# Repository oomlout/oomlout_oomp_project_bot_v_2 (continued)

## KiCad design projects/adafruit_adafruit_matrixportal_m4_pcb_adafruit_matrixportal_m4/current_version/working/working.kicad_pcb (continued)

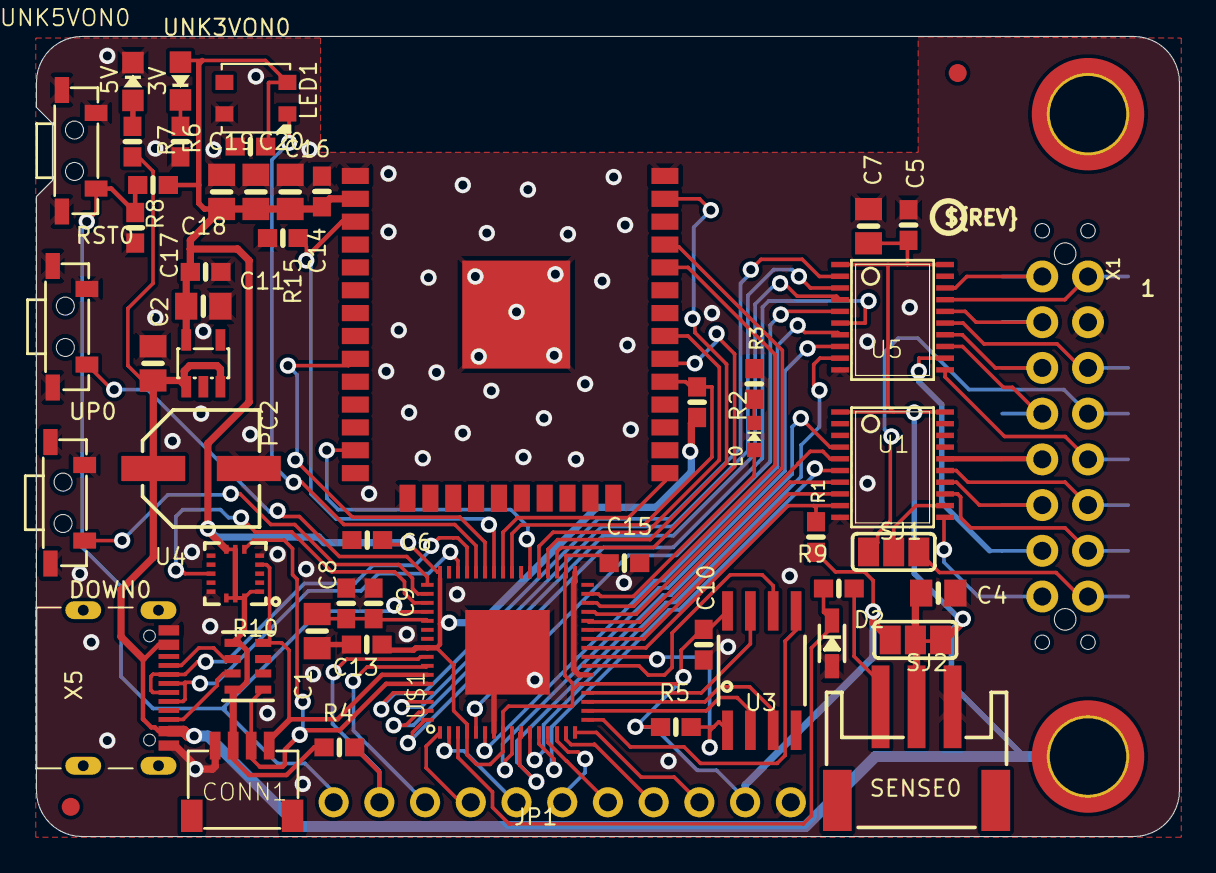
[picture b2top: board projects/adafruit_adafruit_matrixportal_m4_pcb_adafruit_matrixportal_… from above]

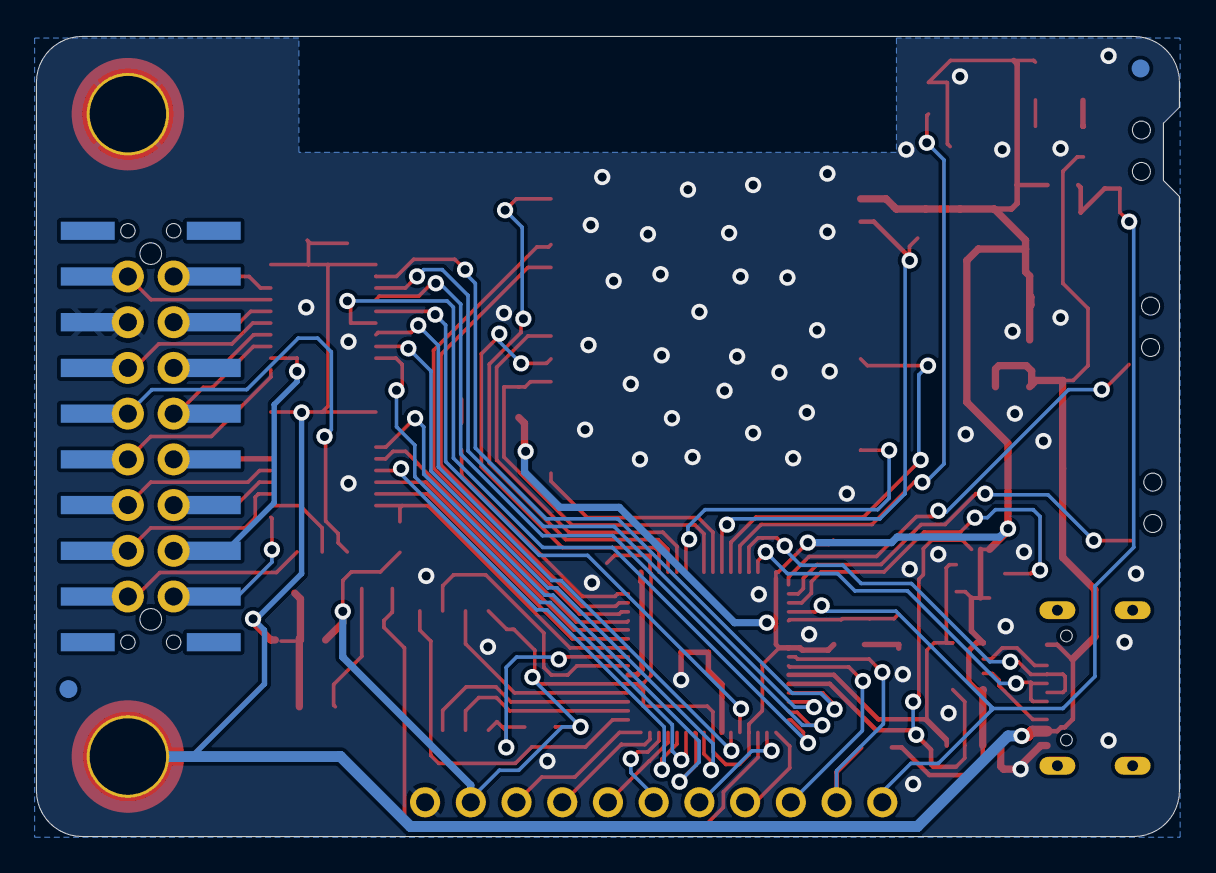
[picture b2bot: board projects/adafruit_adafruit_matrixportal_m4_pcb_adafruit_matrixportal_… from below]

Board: 2 copper layers, 63.5 x 44.5 mm, 62 parts (3 on the bottom side), 76 nets.

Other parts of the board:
U$41: MATRIXPORTAL_BOT
U$44: PCBFEAT-REV-040
U$45: MATRIXPORTAL_TOP

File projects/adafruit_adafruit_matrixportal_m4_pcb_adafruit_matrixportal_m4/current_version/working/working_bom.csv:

"Id";"Designator";"Footprint";"Quantity";"Designation";"Supplier and ref";
1;"R4,R9";"0603-NO";2;"1K";;;
2;"SENSE0";"JSTPH3";1;"JST PH 3";;;
3;"C3,C7,C2,C4,C19,C1,C18,C20";"0805-NO";8;"10uF";;;
4;"L0";"CHIPLED_0603_NOOUTLINE";1;"RED";;;
5;"U2";"SOT23-DBV";1;"AP2112K-3.3";;;
6;"D2";"SOD-323";1;"3.6V";;;
7;"C16,C6,C15,C11,C8,C10,C14";"0603-NO";7;".1u";;;
8;"C5,C17,C13";"0603-NO";3;"0.1uF";;;
9;"U$44";"PCBFEAT-REV-040";1;"";;;
10;"RST0,UP0,DOWN0";"SPST_TACTILE_RA";3;"TL3330AF260QG";;;
11;"TP2,TP1";"SMT_NUT_3MM";2;"SEWTAP_SMTNUTM3";;;
12;"LED1";"LED3535";1;"WS2812B3535";;;
13;"R15,R5,R1,R2,R6,R7";"0603-NO";6;"10K";;;
14;"U3";"SOIC8_208MIL";1;"GD25Q16";;;
15;"CONN1";"JST_SH4";1;"STEMMA_I2C_QT";;;
16;"X6";"WROOM32";1;"ESP32_WROOM32";;;
17;"R8,R3";"0603-NO";2;"5.1K";;;
18;"UNK3VON0,UNK5VON0";"CHIPLED_0805_NOOUTLINE";2;"GREEN";;;
19;"SJ2,SJ1";"SOLDERJUMPER_2WAY_OPEN_NOPASTE";2;"";;;
20;"FID2,FID1,FID3,FID4";"FIDUCIAL_1MM";4;"FIDUCIAL_1MM";;;
21;"JP1";"1X11_ROUND";1;"";;;
22;"U$45";"MATRIXPORTAL_TOP";1;"";;;
23;"U$1";"PQFN64-1";1;"ATSAMD51J19";;;
24;"R10";"RESPACK_4X0603";1;"5.1K";;;
25;"PC2";"PANASONIC_D";1;"47uF+/6.3V+";;;
26;"C9";"0603-NO";1;"1uF";;;
27;"U5,U1";"TSSOP20";2;"74AHCT245";;;
28;"X5";"USB_C_CUSB31-CFM2AX-01-X";1;"USB TYPE C";;;
29;"U4";"LGA16_3X3MM";1;"LIS3DHTR";;;
30;"X1";"2X08_SMTTHM_RGBMATRIX";1;"RGBMATRIX_THMSMT";;;
31;"U$41";"MATRIXPORTAL_BOT";1;"";;;

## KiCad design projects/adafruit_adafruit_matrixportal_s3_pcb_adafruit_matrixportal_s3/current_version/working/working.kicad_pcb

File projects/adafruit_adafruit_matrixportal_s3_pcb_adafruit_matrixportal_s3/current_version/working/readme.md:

# adafruit_matrixportal_s3_pcb
 
## summary 
* id: adafruit_adafruit_matrixportal_s3_pcb_adafruit_matrixportal_s3
* user: adafruit
* name: adafruit_matrixportal_s3_pcb
* board: adafruit_matrixportal_s3
* repo: https://github.com/adafruit/Adafruit-MatrixPortal-S3-PCB

* src_file_repo_sch: 
* src_file_repo_sch_link: https://github.com/adafruit/Adafruit-MatrixPortal-S3-PCB/tree/main/
* full details link: https://github.com/oomlout/oomlout_oomp_project_bot_v_2/tree/main/projects/adafruit_adafruit_matrixportal_s3_pcb_adafruit_matrixportal_s3/current_version/working  

## schematic  
  
[schematic (pdf)](working_schematic.pdf) 

## pcb  

[board (pdf)](working.pdf)  

## working_bom
| Id | Designator | Footprint | Quantity | Designation | Supplier and ref |  | None | 
| --- | --- | --- | --- | --- | --- | --- | --- | 
| 1 | SW1 | BTN_RKB2_4.6X2.8 | 1 | KMR2 |  |  | [''] | 
| 2 | C10,C14,C5,C15,C11 | 0603-NO | 5 | 0.1uF |  |  | [''] | 
| 3 | D2 | SOD-323 | 1 | 3.6V |  |  | [''] | 
| 4 | SJ1,SJ2 | SOLDERJUMPER_2WAY_OPEN_NOPASTE | 2 |  |  |  | [''] | 
| 5 | C23,C2,C18,C22,C7,C20,C19,C4,C3 | 0805-NO | 9 | 10uF |  |  | [''] | 
| 6 | U$25 | S3_MATRIXPORTAL_TOP | 1 |  |  |  | [''] | 
| 7 | UNK3VON0,UNK5VON0 | CHIPLED_0603_NOOUTLINE | 2 | GREEN |  |  | [''] | 
| 8 | CONN1 | JST_SH4 | 1 | STEMMA_I2C_QT |  |  | [''] | 
| 9 | C21,C24,C17 | 0603-NO | 3 | 1uF |  |  | [''] | 
| 10 | R10 | RESPACK_4X0603 | 1 | 5.1K Pack |  |  | [''] | 
| 11 | R16,R3,R1,R2,R7,R6 | 0603-NO | 6 | 10K |  |  | [''] | 
| 12 | SENSE0 | JSTPH3 | 1 | JST PH 3 |  |  | [''] | 
| 13 | LED1 | LED3535_FULLPADS | 1 | WS2812B_3535FULL |  |  | [''] | 
| 14 | U3 | S3-WROOM32 | 1 | ESP32-S3-WROOM |  |  | [''] | 
| 15 | U$44 | PCBFEAT-REV-040 | 1 |  |  |  | [''] | 
| 16 | L0 | CHIPLED_0603_NOOUTLINE | 1 | RED |  |  | [''] | 
| 17 | FID2,FID1,FID3,FID4 | FIDUCIAL_1MM | 4 | FIDUCIAL_1MM |  |  | [''] | 
| 18 | JP1 | 1X11_ROUND | 1 |  |  |  | [''] | 
| 19 | U$14,U$22,U$24,U$19 | MOUNTINGHOLE_2.5_PLATED | 4 | MOUNTINGHOLE2.5 |  |  | [''] | 
| 20 | U1,U5 | TSSOP20 | 2 | 74AHCT245 |  |  | [''] | 
| 21 | UP0,DOWN0,RST0 | SPST_TACTILE_RA | 3 | TL3330AF260QG |  |  | [''] | 
| 22 | TP2,TP1 | SMT_NUT_3MM | 2 | SEWTAP_SMTNUTM3 |  |  | [''] | 
| 23 | R9 | 0603-NO | 1 | 1K |  |  | [''] | 
| 24 | U6 | ALS-PT19-315C | 1 | ALS-PT19 |  |  | [''] | 
| 25 | PC2 | PANASONIC_D | 1 | 100uF/6.3V |  |  | [''] | 
| 26 | U2 | SOT23-DBV | 1 | AP2112K-3.3 |  |  | [''] | 
| 27 | R17 | 0603-NO | 1 | 1Meg |  |  | [''] | 
| 28 | U4 | LGA16_3X3MM | 1 | LIS3DHTR |  |  | [''] | 
| 29 | JP2 | 2X08_SHROUDEDSMT | 1 | 2x8_SMT_IDC |  |  | [''] | 
| 30 | X5 | USB_C_CUSB31-CFM2AX-01-X | 1 | USB TYPE C |  |  | [''] | 
| 31 | U$26 | S3_MATRIXPORTAL_BOT | 1 |  |  |  | [''] | 
| 32 | JP3 | 2X10_SMT_FEMALE | 1 | 2x10_SMT_F |  |  | [''] | 

## bom_schematic
| Ref | Qnty | Value | Cmp name | Footprint | Description | Vendor | DNP | 
| --- | --- | --- | --- | --- | --- | --- | --- | 
| C2, C3, C4, C7, C18, C19, C20, C22, C23 | 9 | 10uF | CAP_CERAMIC0805-NOOUTLINE | working:0805-NO |  |  |  | 
| C5, C10, C11, C14, C15 | 5 | 0.1uF | CAP_CERAMIC0603_NO | working:0603-NO |  |  |  | 
| C17, C21, C24 | 3 | 1uF | CAP_CERAMIC0603_NO | working:0603-NO |  |  |  | 
| CONN1 | 1 | STEMMA_I2C_QT | STEMMA_I2C_QT | working:JST_SH4 |  |  |  | 
| D2 | 1 | 3.6V | DIODE-ZENERSOD323 | working:SOD-323 |  |  |  | 
| DOWN0 | 1 | TL3330AF260QG | SWITCH_SPST_MNT_TACT_RA | working:SPST_TACTILE_RA |  |  |  | 
| FID1, FID2, FID3, FID4 | 4 | FIDUCIAL_1MM | FIDUCIAL_1MM | working:FIDUCIAL_1MM |  |  |  | 
| JP1 | 1 | HEADER-1X11 | HEADER-1X11 | working:1X11_ROUND |  |  |  | 
| JP2 | 1 | 2x8_SMT_IDC | HEADER-2X8_SHROUDEDSMT | working:2X08_SHROUDEDSMT |  |  |  | 
| JP3 | 1 | 2x10_SMT_F | HEADER-2X10SMT_FEMALE | working:2X10_SMT_FEMALE |  |  |  | 
| L0 | 1 | RED | LED0603_NOOUTLINE | working:CHIPLED_0603_NOOUTLINE |  |  |  | 
| LED1 | 1 | WS2812B_3535FULL | WS2812B_3535FULL | working:LED3535_FULLPADS |  |  |  | 
| PC2 | 1 | 100uF/6.3V | CAP_ELECTROLYTICPANASONIC_D | working:PANASONIC_D |  |  |  | 
| R1, R2, R3, R6, R7, R16 | 6 | 10K | RESISTOR_0603_NOOUT | working:0603-NO |  |  |  | 
| R9 | 1 | 1K | RESISTOR_0603_NOOUT | working:0603-NO |  |  |  | 
| R10 | 1 | 5.1K Pack | RESISTOR_4PACK | working:RESPACK_4X0603 |  |  |  | 
| R17 | 1 | 1Meg | RESISTOR_0603_NOOUT | working:0603-NO |  |  |  | 
| RST0 | 1 | TL3330AF260QG | SWITCH_SPST_MNT_TACT_RA | working:SPST_TACTILE_RA |  |  |  | 
| SENSE0 | 1 | JST PH 3 | CON_JST_PH_3PIN | working:JSTPH3 |  |  |  | 
| SJ1, SJ2 | 2 | SOLDERJUMPER_2WAY | SOLDERJUMPER_2WAY | working:SOLDERJUMPER_2WAY_OPEN_NOPASTE |  |  |  | 
| SW1 | 1 | KMR2 | SWITCH_TACT_SMT_RKB2 | working:BTN_RKB2_4.6X2.8 |  |  |  | 
| TP1, TP2 | 2 | SEWTAP_SMTNUTM3 | SEWTAP_SMTNUTM3 | working:SMT_NUT_3MM |  |  |  | 
| U1, U5 | 2 | 74AHCT245 | 74LCX245_TSSOP20 | working:TSSOP20 |  |  |  | 
| U2 | 1 | LP2985-XXDBVR | LP2985-XXDBVR | working:SOT23-DBV |  |  |  | 
| U3 | 1 | ESP32-S3-WROOM | ESP32-S3-WROOM | working:S3-WROOM32 |  |  |  | 
| U4 | 1 | LIS3DHTR | ACCEL_LIS3DHTR | working:LGA16_3X3MM |  |  |  | 
| U6 | 1 | ALS-PT19 | PHOTOTRANSISTOR_PT19-315C | working:ALS-PT19-315C |  |  |  | 
| U$14, U$19, U$22, U$24 | 4 | MOUNTINGHOLE2.5 | MOUNTINGHOLE2.5 | working:MOUNTINGHOLE_2.5_PLATED |  |  |  | 
| UNK3VON0 | 1 | GREEN | LED0603_NOOUTLINE | working:CHIPLED_0603_NOOUTLINE |  |  |  | 
| UNK5VON0 | 1 | GREEN | LED0603_NOOUTLINE | working:CHIPLED_0603_NOOUTLINE |  |  |  | 
| UP0 | 1 | TL3330AF260QG | SWITCH_SPST_MNT_TACT_RA | working:SPST_TACTILE_RA |  |  |  | 
| X5 | 1 | USB TYPE C | USB_C | working:USB_C_CUSB31-CFM2AX-01-X |  |  |  | 

## mounting_holes
| x | y | package | value | ref | size | 
| --- | --- | --- | --- | --- | --- | 
| 0.0 | 0.0 | MOUNTINGHOLE_2.5_PLATED | MOUNTINGHOLE2.5 | U$14 | m3 | 
| 0.0 | 19.69 | MOUNTINGHOLE_2.5_PLATED | MOUNTINGHOLE2.5 | U$19 | m3 | 
| 40.64 | 19.69 | MOUNTINGHOLE_2.5_PLATED | MOUNTINGHOLE2.5 | U$22 | m3 | 
| 40.64 | 0.0 | MOUNTINGHOLE_2.5_PLATED | MOUNTINGHOLE2.5 | U$24 | m3 |

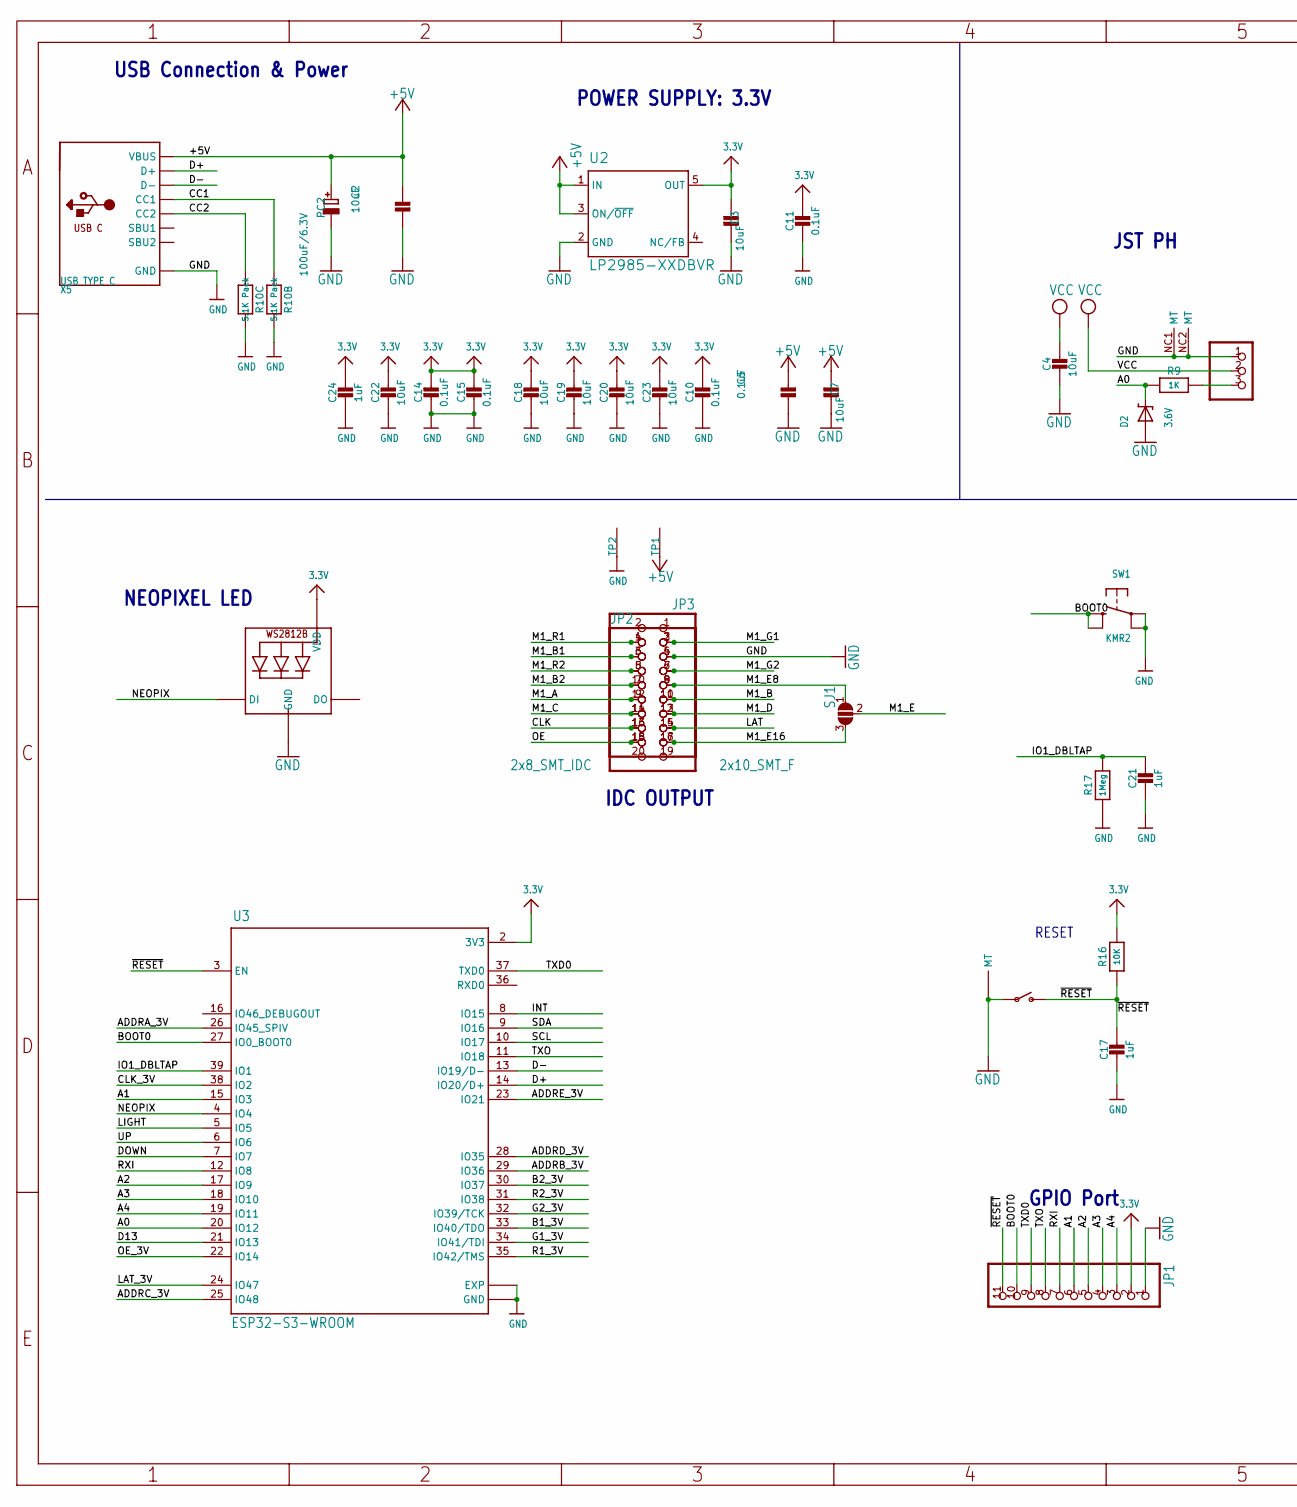
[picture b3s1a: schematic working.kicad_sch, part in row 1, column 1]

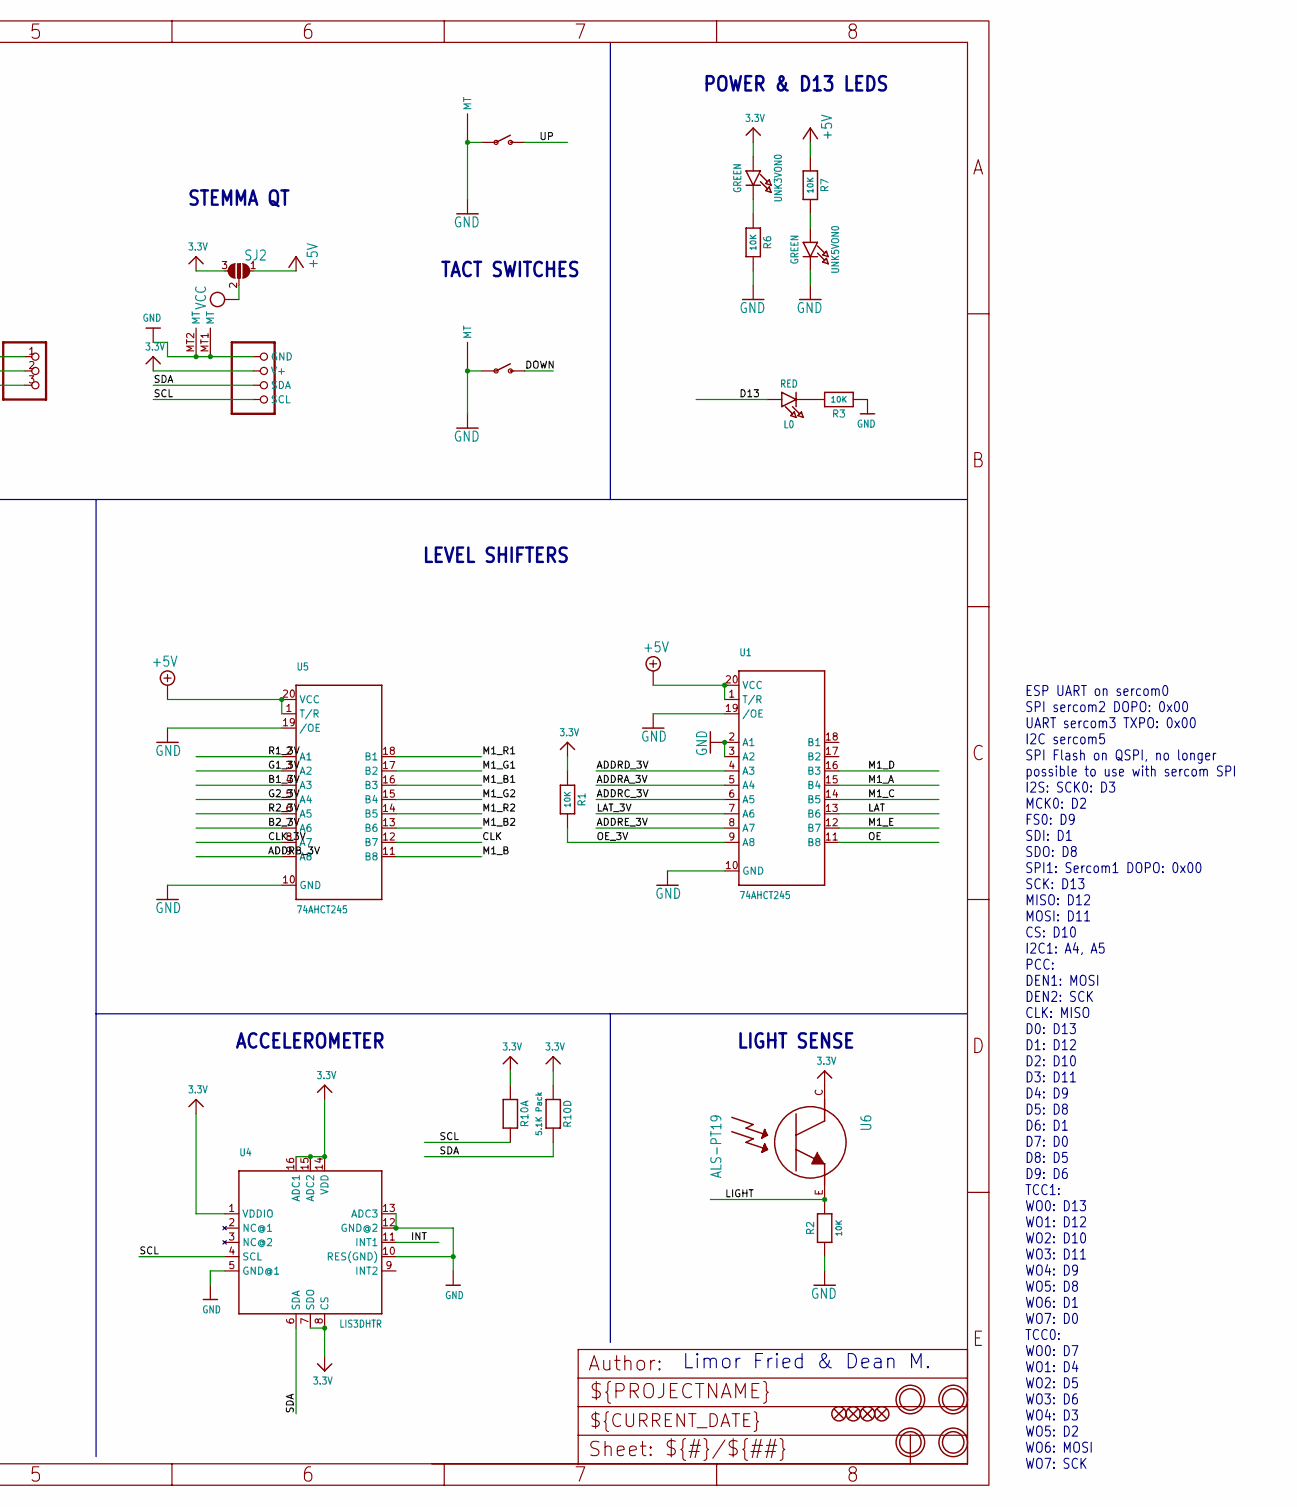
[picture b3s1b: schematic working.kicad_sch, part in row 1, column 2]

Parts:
C2, C3, C4, C7, C18, C19, C20, C22, C23: 10uF; 0805-NO
C5, C10, C11, C14, C15: 0.1uF; 0603-NO
C17, C21, C24: 1uF; 0603-NO
CONN1: STEMMA_I2C_QT; JST_SH4
D2: 3.6V; SOD-323
DOWN0: TL3330AF260QG; SPST_TACTILE_RA
FID1, FID2, FID3, FID4: FIDUCIAL_1MM
JP1: HEADER-1X11; 1X11_ROUND
JP2: 2x8_SMT_IDC; 2X08_SHROUDEDSMT
JP3: 2x10_SMT_F; 2X10_SMT_FEMALE
L0: RED; CHIPLED_0603_NOOUTLINE
LED1: WS2812B_3535FULL; LED3535_FULLPADS
PC2: 100uF/6.3V; PANASONIC_D
R1, R2, R3, R6, R7, R16: 10K; 0603-NO
R9: 1K; 0603-NO
R10: 5.1K Pack; RESPACK_4X0603
R17: 1Meg; 0603-NO
RST0: TL3330AF260QG; SPST_TACTILE_RA
SENSE0: JST PH 3; JSTPH3
SJ1, SJ2: SOLDERJUMPER_2WAY; SOLDERJUMPER_2WAY_OPEN_NOPASTE
SW1: KMR2; BTN_RKB2_4.6X2.8
TP1, TP2: SEWTAP_SMTNUTM3; SMT_NUT_3MM
U1, U5: 74AHCT245; TSSOP20
U2: LP2985-XXDBVR; SOT23-DBV
U3: ESP32-S3-WROOM; S3-WROOM32
U4: LIS3DHTR; LGA16_3X3MM
U6: ALS-PT19; ALS-PT19-315C
U$14, U$19, U$22, U$24: MOUNTINGHOLE2.5; MOUNTINGHOLE_2.5_PLATED
UNK3VON0, UNK5VON0: GREEN; CHIPLED_0603_NOOUTLINE
UP0: TL3330AF260QG; SPST_TACTILE_RA
X5: USB TYPE C; USB_C_CUSB31-CFM2AX-01-X

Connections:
3.3V: C3.2, C10.2, C11.2, C14.2, C15.2, C18.1, C19.1, C20.1, C22.1, C23.1, C24.1, CONN1.2 (V+), JP1.2, LED1.2 (VDD), R1.1, R10.1, R10.4 (1), R16.2, SJ2.3, U2.5 (OUT), U3.2 (3V3), U4.1 (VDDIO), U4.7 (SDO), U4.8 (CS), U4.14 (VDD), U4.15 (ADC2), U4.16 (ADC1), U6.C, UNK3VON0.A
+5V: C2.2, C5.2, C7.2, PC2.+, R7.1, SJ2.1, TP1.P$1, U1.1 (T/R), U1.20 (VCC), U2.1 (IN), U2.3 (ON/~OFF), U5.1 (T/R), U5.20 (VCC), X5.A4B9 (VBUS), X5.B4A9 (VBUS)
A0: D2.C, R9.2, U3.20 (IO12)
A0_JST: R9.1, SENSE0.3
A1: JP1.6, U3.15 (IO3)
A2: JP1.5, U3.17 (IO9)
A3: JP1.4, U3.18 (IO10)
A4: JP1.3, U3.19 (IO11)
ADDRA_3V: U1.5 (A4), U3.26 (IO45_SPIV)
ADDRB_3V: U3.29 (IO36), U5.9 (A8)
ADDRC_3V: U1.6 (A5), U3.25 (IO48)
ADDRD_3V: U1.4 (A3), U3.28 (IO35)
ADDRE_3V: U1.8 (A7), U3.23 (IO21)
B1_3V: U3.33 (IO40/TDO), U5.4 (A3)
B2_3V: U3.30 (IO37), U5.7 (A6)
BOOT0: JP1.10, SW1.B (S), SW1.B' (S1), U3.27 (IO0_BOOT0)
CC1: R10.2 (1), X5.A5 (CC1)
CC2: R10.3 (1), X5.B5 (CC2)
CLK: JP2.13, JP3.16, U5.12 (B7)
CLK_3V: U3.38 (IO2), U5.8 (A7)
D13: L0.A, U3.21 (IO13)
D+: U3.14 (IO20/D+), X5.A6 (D+), X5.B6 (D+)
D-: U3.13 (IO19/D-), X5.A7 (D-), X5.B7 (D-)
DOWN: DOWN0.2 (S), U3.7 (IO7)
G1_3V: U3.34 (IO41/TDI), U5.3 (A2)
G2_3V: U3.32 (IO39/TCK), U5.5 (A4)
GND: C2.1, C3.1, C4.2, C5.1, C7.1, C10.1, C11.1, C14.1, C15.1, C17.2, C18.2, C19.2, C20.2, C21.2, C22.2, C23.2, C24.2, CONN1.1 (GND), CONN1.MT1 (MT), CONN1.MT2 (MT), D2.A, DOWN0.1, DOWN0.MT1 (MT), DOWN0.MT2 (MT), JP1.1, JP2.4, JP3.5, LED1.4 (GND), PC2.-, R2.2, R3.2, R6.2, R10.6 (2), R10.7 (2), R17.1, RST0.1, RST0.MT1 (MT), RST0.MT2 (MT), SENSE0.1, SENSE0.NC1 (MT), SENSE0.NC2 (MT), SW1.A, SW1.A' (P1), TP2.P$1, U1.2 (A1), U1.3 (A2), U1.10 (GND), U1.19 (/OE), U2.2 (GND), U3.1 (GND), U3.40 (GND), U3.P$2 (EXP), U3.P$3 (EXP), U3.P$4 (EXP), U3.P$5 (EXP), U3.P$6 (EXP), U3.P$7 (EXP), U3.P$8 (EXP), U3.P$9 (EXP), U3.P$10 (EXP), U4.5 (GND@1), U4.10 (RES(GND)), U4.12 (GND@2), U4.13 (ADC3), U5.10 (GND), U5.19 (/OE), UNK5VON0.C, UP0.1, UP0.MT1 (MT), UP0.MT2 (MT), X5.A1B12 (GND), X5.B1A12 (GND)
INT: U3.8 (IO15), U4.11 (INT1)
IO1_DBLTAP: C21.1, R17.2, U3.39 (IO1)
LAT: JP2.14, JP3.15, U1.13 (B6)
LAT_3V: U1.7 (A6), U3.24 (IO47)
LIGHT: R2.1, U3.5 (IO5), U6.E
M1_A: JP2.9, JP3.12, U1.15 (B4)
M1_B: JP2.10, JP3.11, U5.11 (B8)
M1_B1: JP2.3, JP3.6, U5.16 (B3)
M1_B2: JP2.7, JP3.10, U5.13 (B6)
M1_C: JP2.11, JP3.14, U1.14 (B5)
M1_D: JP2.12, JP3.13, U1.16 (B3)
M1_E: SJ1.2, U1.12 (B7)
M1_E8: JP2.8, JP3.9, SJ1.1
M1_E16: JP2.16, JP3.17, SJ1.3
M1_G1: JP2.2, JP3.3, U5.17 (B2)
M1_G2: JP2.6, JP3.7, U5.15 (B4)
M1_R1: JP2.1, JP3.4, U5.18 (B1)
M1_R2: JP2.5, JP3.8, U5.14 (B5)
unnamed: R7.2, UNK5VON0.A
unnamed: R6.1, UNK3VON0.C
unnamed: L0.C, R3.1
NEOPIX: LED1.1 (DI), U3.4 (IO4)
OE: JP2.15, JP3.18, U1.11 (B8)
OE_3V: R1.2, U1.9 (A8), U3.22 (IO14)
R1_3V: U3.35 (IO42/TMS), U5.2 (A1)
R2_3V: U3.31 (IO38), U5.6 (A5)
RXI: JP1.7, U3.12 (IO8)
SCL: CONN1.4 (SCL), R10.8 (2), U3.10 (IO17), U4.4 (SCL)
SDA: CONN1.3 (SDA), R10.5 (2), U3.9 (IO16), U4.6 (SDA)
TXD0: JP1.9, U3.37 (TXD0)
TXO: JP1.8, U3.11 (IO18)
UP: U3.6 (IO6), UP0.2 (S)
VCC: C4.1, SENSE0.2, SJ2.2
~RESET: C17.1, JP1.11, R16.1, RST0.2 (S), U3.3 (EN)

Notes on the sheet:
POWER SUPPLY: 3.3V
ACCELEROMETER
JST PH
POWER & D13 LEDS
LIGHT SENSE
RESET
LEVEL SHIFTERS
USB Connection & Power
GPIO Port
ESP UART on sercom0 SPI sercom2 DOPO: 0x00 UART sercom3 TXPO: 0x00 I2C sercom5 SPI Flash on QSPI, no longer possible to use with sercom SPI I2S: SCK0: D3 MCK0: D2 FS0: D9 SDI: D1 SDO: D8 SPI1: Sercom1 DOPO: 0x00 SCK: D13 MISO: D12 MOSI: D11 CS: D10 I2C1: A4, A5 PCC: DEN1: MOSI DEN2: SCK CLK: MISO D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
Limor Fried & Dean M.
STEMMA QT
TACT SWITCHES
IDC OUTPUT
NEOPIXEL LED

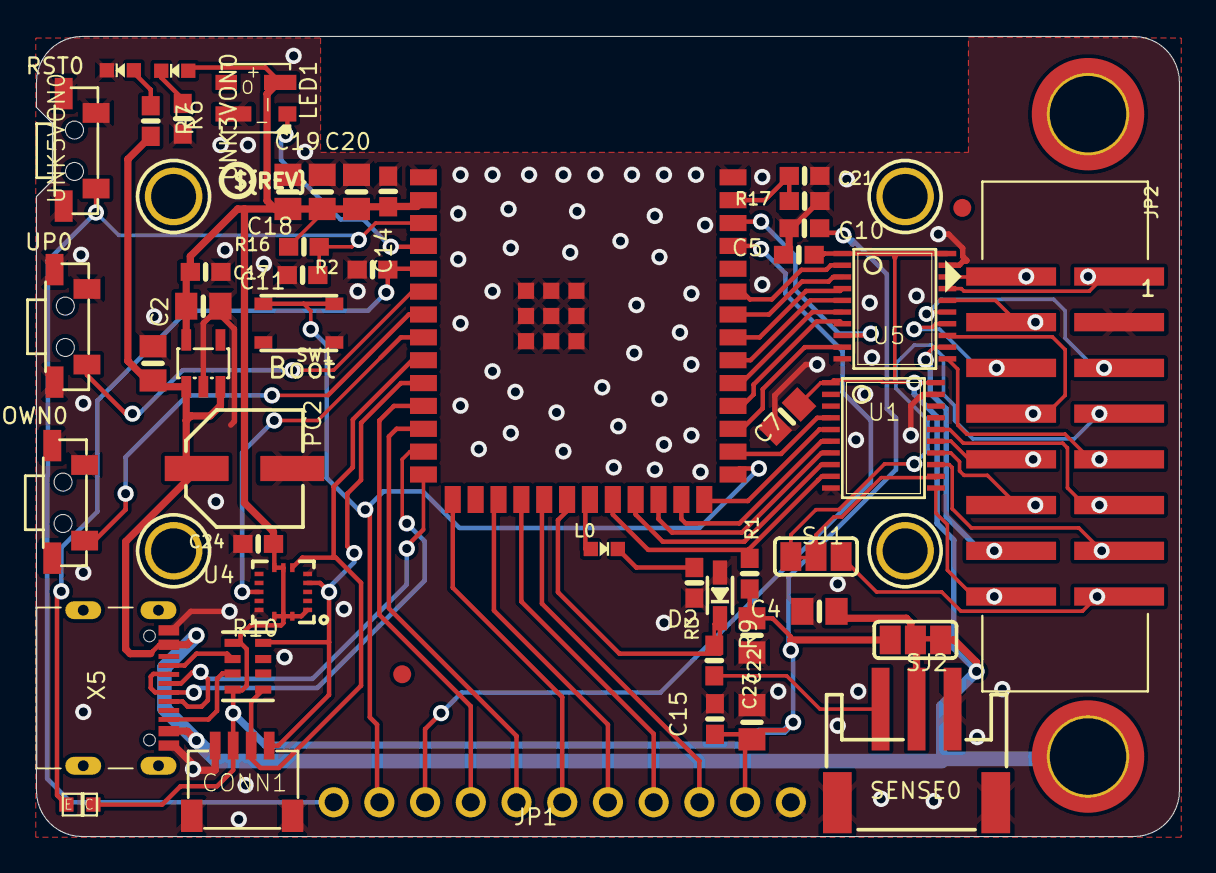
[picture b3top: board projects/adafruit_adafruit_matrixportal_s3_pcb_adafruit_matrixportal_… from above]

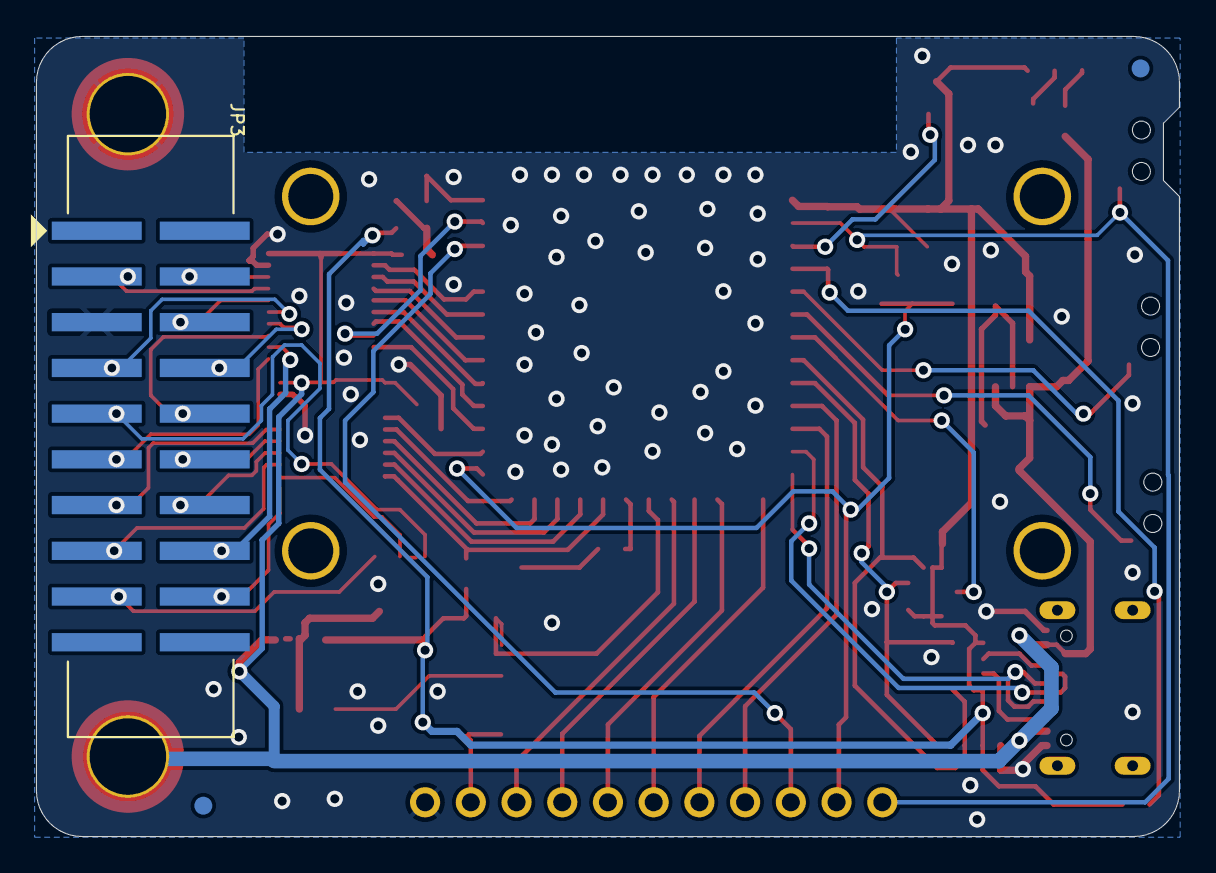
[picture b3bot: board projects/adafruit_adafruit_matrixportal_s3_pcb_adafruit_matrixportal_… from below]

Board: 2 copper layers, 63.5 x 44.5 mm, 63 parts (4 on the bottom side), 61 nets.

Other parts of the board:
U$25: S3_MATRIXPORTAL_TOP
U$26: S3_MATRIXPORTAL_BOT
U$44: PCBFEAT-REV-040

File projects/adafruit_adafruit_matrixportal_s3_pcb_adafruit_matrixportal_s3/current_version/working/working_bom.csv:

"Id";"Designator";"Footprint";"Quantity";"Designation";"Supplier and ref";
1;"SW1";"BTN_RKB2_4.6X2.8";1;"KMR2";;;
2;"C10,C14,C5,C15,C11";"0603-NO";5;"0.1uF";;;
3;"D2";"SOD-323";1;"3.6V";;;
4;"SJ1,SJ2";"SOLDERJUMPER_2WAY_OPEN_NOPASTE";2;"";;;
5;"C23,C2,C18,C22,C7,C20,C19,C4,C3";"0805-NO";9;"10uF";;;
6;"U$25";"S3_MATRIXPORTAL_TOP";1;"";;;
7;"UNK3VON0,UNK5VON0";"CHIPLED_0603_NOOUTLINE";2;"GREEN";;;
8;"CONN1";"JST_SH4";1;"STEMMA_I2C_QT";;;
9;"C21,C24,C17";"0603-NO";3;"1uF";;;
10;"R10";"RESPACK_4X0603";1;"5.1K Pack";;;
11;"R16,R3,R1,R2,R7,R6";"0603-NO";6;"10K";;;
12;"SENSE0";"JSTPH3";1;"JST PH 3";;;
13;"LED1";"LED3535_FULLPADS";1;"WS2812B_3535FULL";;;
14;"U3";"S3-WROOM32";1;"ESP32-S3-WROOM";;;
15;"U$44";"PCBFEAT-REV-040";1;"";;;
16;"L0";"CHIPLED_0603_NOOUTLINE";1;"RED";;;
17;"FID2,FID1,FID3,FID4";"FIDUCIAL_1MM";4;"FIDUCIAL_1MM";;;
18;"JP1";"1X11_ROUND";1;"";;;
19;"U$14,U$22,U$24,U$19";"MOUNTINGHOLE_2.5_PLATED";4;"MOUNTINGHOLE2.5";;;
20;"U1,U5";"TSSOP20";2;"74AHCT245";;;
21;"UP0,DOWN0,RST0";"SPST_TACTILE_RA";3;"TL3330AF260QG";;;
22;"TP2,TP1";"SMT_NUT_3MM";2;"SEWTAP_SMTNUTM3";;;
23;"R9";"0603-NO";1;"1K";;;
24;"U6";"ALS-PT19-315C";1;"ALS-PT19";;;
25;"PC2";"PANASONIC_D";1;"100uF/6.3V";;;
26;"U2";"SOT23-DBV";1;"AP2112K-3.3";;;
27;"R17";"0603-NO";1;"1Meg";;;
28;"U4";"LGA16_3X3MM";1;"LIS3DHTR";;;
29;"JP2";"2X08_SHROUDEDSMT";1;"2x8_SMT_IDC";;;
30;"X5";"USB_C_CUSB31-CFM2AX-01-X";1;"USB TYPE C";;;
31;"U$26";"S3_MATRIXPORTAL_BOT";1;"";;;
32;"JP3";"2X10_SMT_FEMALE";1;"2x10_SMT_F";;;

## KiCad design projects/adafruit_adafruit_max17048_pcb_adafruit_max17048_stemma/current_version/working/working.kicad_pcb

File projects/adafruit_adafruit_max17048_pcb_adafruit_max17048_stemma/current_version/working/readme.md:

# adafruit_max17048_pcb
 
## summary 
* id: adafruit_adafruit_max17048_pcb_adafruit_max17048_stemma
* user: adafruit
* name: adafruit_max17048_pcb
* board: adafruit_max17048_stemma
* repo: https://github.com/adafruit/Adafruit-MAX17048-PCB

* src_file_repo_sch: 
* src_file_repo_sch_link: https://github.com/adafruit/Adafruit-MAX17048-PCB/tree/main/
* full details link: https://github.com/oomlout/oomlout_oomp_project_bot_v_2/tree/main/projects/adafruit_adafruit_max17048_pcb_adafruit_max17048_stemma/current_version/working  

## schematic  
  
[schematic (pdf)](working_schematic.pdf) 

## pcb  

[board (pdf)](working.pdf)  

## working_bom
| Id | Designator | Footprint | Quantity | Designation | Supplier and ref |  | None | 
| --- | --- | --- | --- | --- | --- | --- | --- | 
| 1 | U$19,U$21 | MOUNTINGHOLE_2.5_PLATED | 2 | MOUNTINGHOLE2.5 |  |  | [''] | 
| 2 | X1,X2 | JSTPH2_BATT | 2 | JST 2 PH |  |  | [''] | 
| 3 | C1,C2 | 0603-NO | 2 | 1uF |  |  | [''] | 
| 4 | FID4,FID3 | FIDUCIAL_1MM | 2 | FIDUCIAL_1MM |  |  | [''] | 
| 5 | @HOLE0,@HOLE1 |  | 2 |  |  |  | [''] | 
| 6 | D1 | CHIPLED_0603_NOOUTLINE | 1 | GREEN |  |  | [''] | 
| 7 | CONN3,CONN4 | JST_SH4 | 2 | STEMMA_I2C_QT |  |  | [''] | 
| 8 | R3 | RESPACK_4X0603 | 1 | 10K |  |  | [''] | 
| 9 | R2 | 0603-NO | 1 | 10K |  |  | [''] | 
| 10 | JP1 | 1X06_ROUND_70 | 1 |  |  |  | [''] | 
| 11 | X3 | TDFN8_2X2MM | 1 | MAX17048/T |  |  | [''] | 
| 12 | U$22 | ADAFRUIT_3.5MM | 1 |  |  |  | [''] | 
| 13 | JP2 | 1X02_ROUND | 1 |  |  |  | [''] | 
| 14 | SJ1 | SOLDERJUMPER_CLOSEDWIRE | 1 |  |  |  | [''] | 
| 15 | U$30,U$31 | STEMMAQT | 2 |  |  |  | [''] | 
| 16 | SJ2 | SOLDERJUMPER_2WAY_OPEN_NOPASTE | 1 |  |  |  | [''] | 
| 17 | U$25 | PCBFEAT-REV-040 | 1 |  |  |  | [''] | 

## bom_schematic
| Ref | Qnty | Value | Cmp name | Footprint | Description | Vendor | DNP | 
| --- | --- | --- | --- | --- | --- | --- | --- | 
| C1, C2 | 2 | 1uF | CAP_CERAMIC0603_NO | working:0603-NO |  |  |  | 
| CONN3, CONN4 | 2 | STEMMA_I2C_QT | STEMMA_I2C_QT | working:JST_SH4 |  |  |  | 
| D1 | 1 | GREEN | LED0603_NOOUTLINE | working:CHIPLED_0603_NOOUTLINE |  |  |  | 
| FID3, FID4 | 2 | FIDUCIAL_1MM | FIDUCIAL_1MM | working:FIDUCIAL_1MM |  |  |  | 
| JP1 | 1 | HEADER-1X670MIL | HEADER-1X670MIL | working:1X06_ROUND_70 |  |  |  | 
| JP2 | 1 | HEADER-1X2ROUND | HEADER-1X2ROUND | working:1X02_ROUND |  |  |  | 
| R2 | 1 | 10K | RESISTOR_0603_NOOUT | working:0603-NO |  |  |  | 
| R3 | 1 | 10K | RESISTOR_4PACK | working:RESPACK_4X0603 |  |  |  | 
| SJ1 | 1 | SOLDERJUMPERCLOSED | SOLDERJUMPERCLOSED | working:SOLDERJUMPER_CLOSEDWIRE |  |  |  | 
| SJ2 | 1 | SOLDERJUMPER_2WAY | SOLDERJUMPER_2WAY | working:SOLDERJUMPER_2WAY_OPEN_NOPASTE |  |  |  | 
| U$19, U$21 | 2 | MOUNTINGHOLE2.5 | MOUNTINGHOLE2.5 | working:MOUNTINGHOLE_2.5_PLATED |  |  |  | 
| X1, X2 | 2 | CON_JST_PH_2PIN_MT_BATT | CON_JST_PH_2PIN_MT_BATT | working:JSTPH2_BATT |  |  |  | 
| X3 | 1 | MAX17048/T | MAX17048/T | working:TDFN8_2X2MM |  |  |  | 

## mounting_holes
| x | y | package | value | ref | size | 
| --- | --- | --- | --- | --- | --- | 
| 0.0 | 0.0 | MOUNTINGHOLE_2.5_PLATED | MOUNTINGHOLE2.5 | U$19 | m3 | 
| 20.32 | 0.0 | MOUNTINGHOLE_2.5_PLATED | MOUNTINGHOLE2.5 | U$21 | m3 |

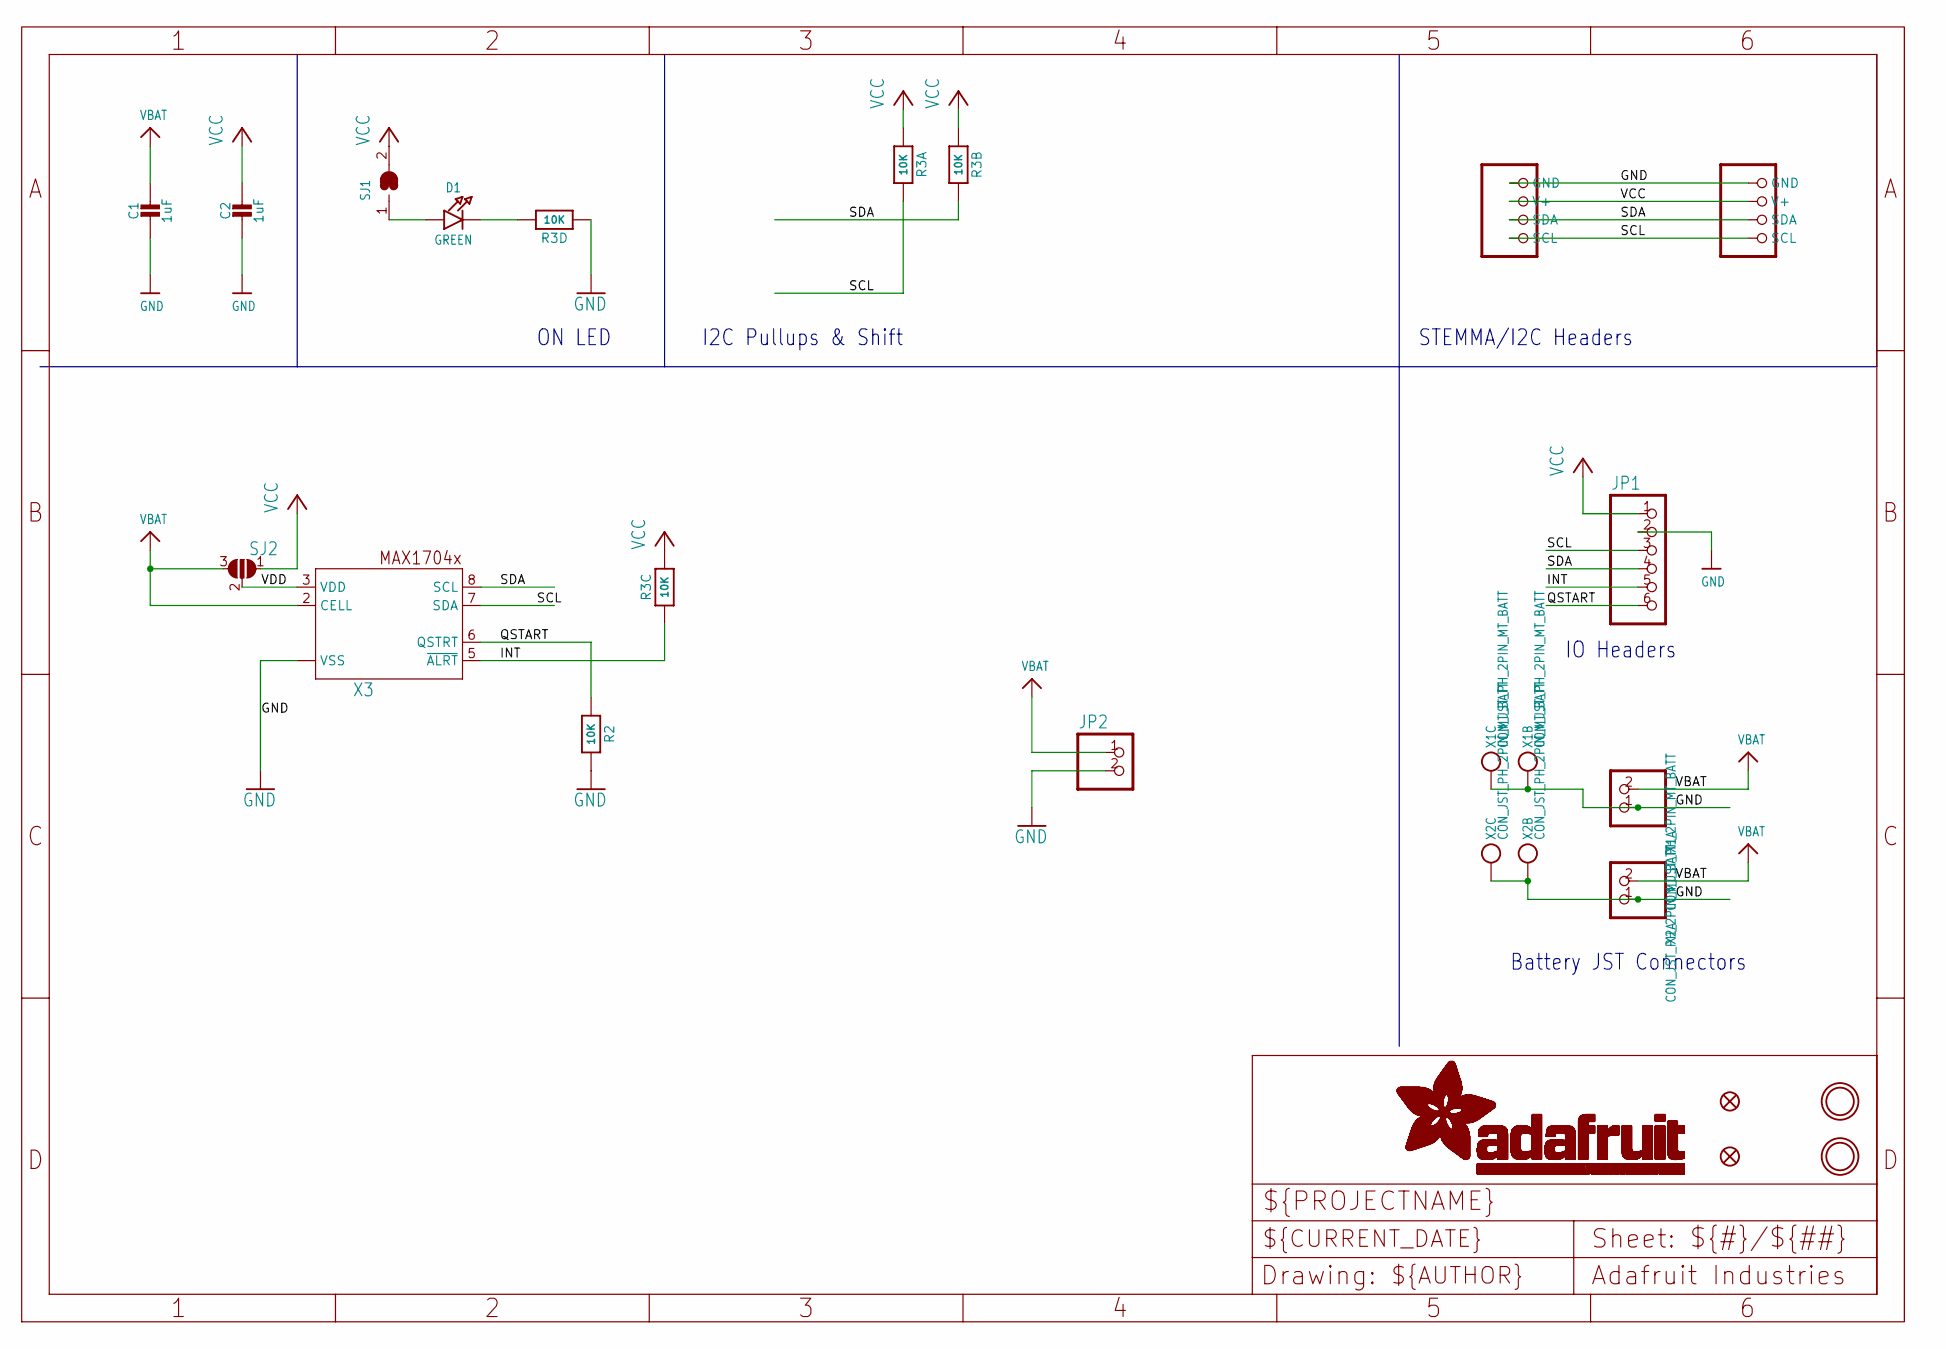
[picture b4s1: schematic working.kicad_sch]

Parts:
C1, C2: 1uF; 0603-NO
CONN3, CONN4: STEMMA_I2C_QT; JST_SH4
D1: GREEN; CHIPLED_0603_NOOUTLINE
FID3, FID4: FIDUCIAL_1MM
JP1: HEADER-1X670MIL; 1X06_ROUND_70
JP2: HEADER-1X2ROUND; 1X02_ROUND
R2: 10K; 0603-NO
R3: 10K; RESPACK_4X0603
SJ1: SOLDERJUMPERCLOSED; SOLDERJUMPER_CLOSEDWIRE
SJ2: SOLDERJUMPER_2WAY; SOLDERJUMPER_2WAY_OPEN_NOPASTE
U$19, U$21: MOUNTINGHOLE2.5; MOUNTINGHOLE_2.5_PLATED
X1, X2: CON_JST_PH_2PIN_MT_BATT; JSTPH2_BATT
X3: MAX17048/T; TDFN8_2X2MM

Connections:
GND: C1.2, C2.2, CONN3.1 (GND), CONN4.1 (GND), JP1.2, JP2.2, R2.2, R3.4 (1), X1.1, X1.NC1, X1.NC2, X2.1, X2.NC1, X2.NC2, X3.1 (VSS), X3.4 (VSS), X3.THERMAL (VSS)
INT: JP1.5, R3.3 (1), X3.5 (~ALRT)
unnamed: D1.C, R3.5 (2)
unnamed: D1.A, SJ1.1
QSTART: JP1.6, R2.1, X3.6 (QSTRT)
SCL: CONN3.4 (SCL), CONN4.4 (SCL), JP1.3, R3.8 (2), X3.7 (SDA)
SDA: CONN3.3 (SDA), CONN4.3 (SDA), JP1.4, R3.7 (2), X3.8 (SCL)
VBAT: C1.1, JP2.1, SJ2.3, X1.2, X2.2, X3.2 (CELL)
VCC: C2.1, CONN3.2 (V+), CONN4.2 (V+), JP1.1, R3.1, R3.2 (1), R3.6 (2), SJ1.2, SJ2.1
VDD: SJ2.2, X3.3 (VDD)

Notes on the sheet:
IO Headers
ON LED
STEMMA/I2C Headers
Battery JST Connectors
I2C Pullups & Shift

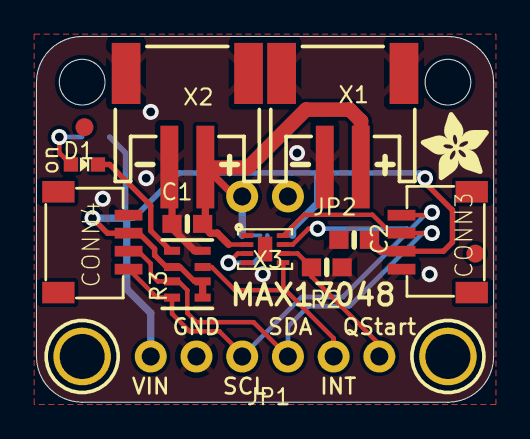
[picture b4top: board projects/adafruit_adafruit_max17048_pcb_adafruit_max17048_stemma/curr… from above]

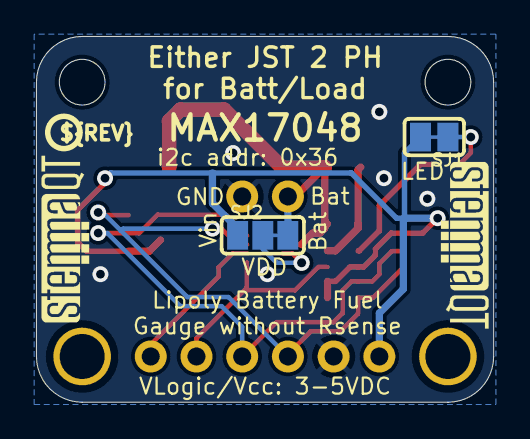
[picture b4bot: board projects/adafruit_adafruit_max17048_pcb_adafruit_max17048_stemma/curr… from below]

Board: 2 copper layers, 25.4 x 20.3 mm, 24 parts (5 on the bottom side), 10 nets.

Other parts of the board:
@HOLE0, @HOLE1: (no value)
U$22: ADAFRUIT_3.5MM
U$25: PCBFEAT-REV-040
U$30, U$31: STEMMAQT

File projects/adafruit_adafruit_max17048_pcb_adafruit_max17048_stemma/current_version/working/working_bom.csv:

"Id";"Designator";"Footprint";"Quantity";"Designation";"Supplier and ref";
1;"U$19,U$21";"MOUNTINGHOLE_2.5_PLATED";2;"MOUNTINGHOLE2.5";;;
2;"X1,X2";"JSTPH2_BATT";2;"JST 2 PH";;;
3;"C1,C2";"0603-NO";2;"1uF";;;
4;"FID4,FID3";"FIDUCIAL_1MM";2;"FIDUCIAL_1MM";;;
5;"@HOLE0,@HOLE1";"";2;"";;;
6;"D1";"CHIPLED_0603_NOOUTLINE";1;"GREEN";;;
7;"CONN3,CONN4";"JST_SH4";2;"STEMMA_I2C_QT";;;
8;"R3";"RESPACK_4X0603";1;"10K";;;
9;"R2";"0603-NO";1;"10K";;;
10;"JP1";"1X06_ROUND_70";1;"";;;
11;"X3";"TDFN8_2X2MM";1;"MAX17048/T";;;
12;"U$22";"ADAFRUIT_3.5MM";1;"";;;
13;"JP2";"1X02_ROUND";1;"";;;
14;"SJ1";"SOLDERJUMPER_CLOSEDWIRE";1;"";;;
15;"U$30,U$31";"STEMMAQT";2;"";;;
16;"SJ2";"SOLDERJUMPER_2WAY_OPEN_NOPASTE";1;"";;;
17;"U$25";"PCBFEAT-REV-040";1;"";;;
